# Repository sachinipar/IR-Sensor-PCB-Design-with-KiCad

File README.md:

# IR-Sensor-PCB-Design-with-KiCad

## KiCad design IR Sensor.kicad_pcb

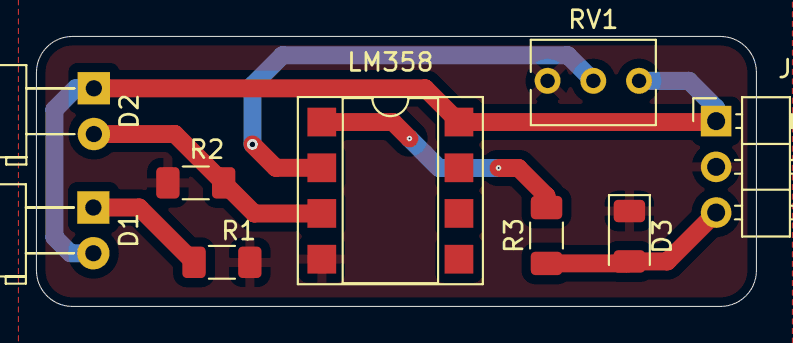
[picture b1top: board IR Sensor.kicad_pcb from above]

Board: 2 copper layers, 40.0 x 15.0 mm, 9 parts (0 on the bottom side), 7 nets.

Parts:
D1, D2: LED; LED_D5.0mm_Horizontal_O3.81mm_Z3.0mm
D3: LED; LED_1206_3216Metric
J1: POWER_CON; PinHeader_1x03_P2.54mm_Horizontal
LM358: LM358; DIP-8_W7.62mm_SMDSocket_SmallPads
R1: 100; R_1206_3216Metric_Pad1.30x1.75mm_HandSolder
R2: 10k; R_1206_3216Metric_Pad1.30x1.75mm_HandSolder
R3: 330; R_1206_3216Metric_Pad1.30x1.75mm_HandSolder
RV1: 10k; Potentiometer_Bourns_3266Y_Vertical

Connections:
+5V: D1.2 (A), D2.1 (K), J1.1, LM358.8 (V+), RV1.1
GND: D3.1 (K), J1.2, LM358.4 (V-), R1.2, R2.2, RV1.3
unnamed: D1.1 (K), R1.1
unnamed: D2.2 (A), LM358.3 (+), R2.1
unnamed: LM358.1, R3.2
unnamed: LM358.2 (-), RV1.2
OUT: D3.2 (A), J1.3, R3.1

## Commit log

2026-02-24 Delete
